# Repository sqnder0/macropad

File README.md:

# Soundpad

A 6-key media soundpad with a rotary encoder and a 0.91" OLED, built around a Seeed XIAO RP2040.

## Features
- 6 MX keys: volume up, mute, volume down, previous, play/pause, next
- Rotary encoder for volume, push to mute
- 128x32 OLED
- KMK firmware

## Schematic

## PCB

## Case
Two printed parts (case and plate), held together by four M3 screws.

## BOM

| Qty | Part | Notes |
| --- | --- | --- |
| 1 | Seeed XIAO RP2040 | Unsoldered, from the kit. Soldered flat to the back of the PCB |
| 6 | MX-style switch | From the kit |
| 6 | White blank DSA keycap | From the kit |
| 1 | EC11E rotary encoder with switch | From the kit, 20 mm D-shaft |
| 1 | Knob cap for the encoder | Not in the kit |
| 1 | 0.91" 128x32 OLED (SSD1306) | From the kit, pin order GND, VCC, SCL, SDA |
| 1 | 1x4 pin header (2.54 mm) | For the OLED |
| 4 | M3x16 mm screw | From the kit |
| 1 | 3D-printed case | Printed |
| 1 | 3D-printed plate | Printed |
| 1 | Custom PCB | Gerbers in `production/gerbers.zip` |

## Firmware
KMK, in `Firmware/main.py`.

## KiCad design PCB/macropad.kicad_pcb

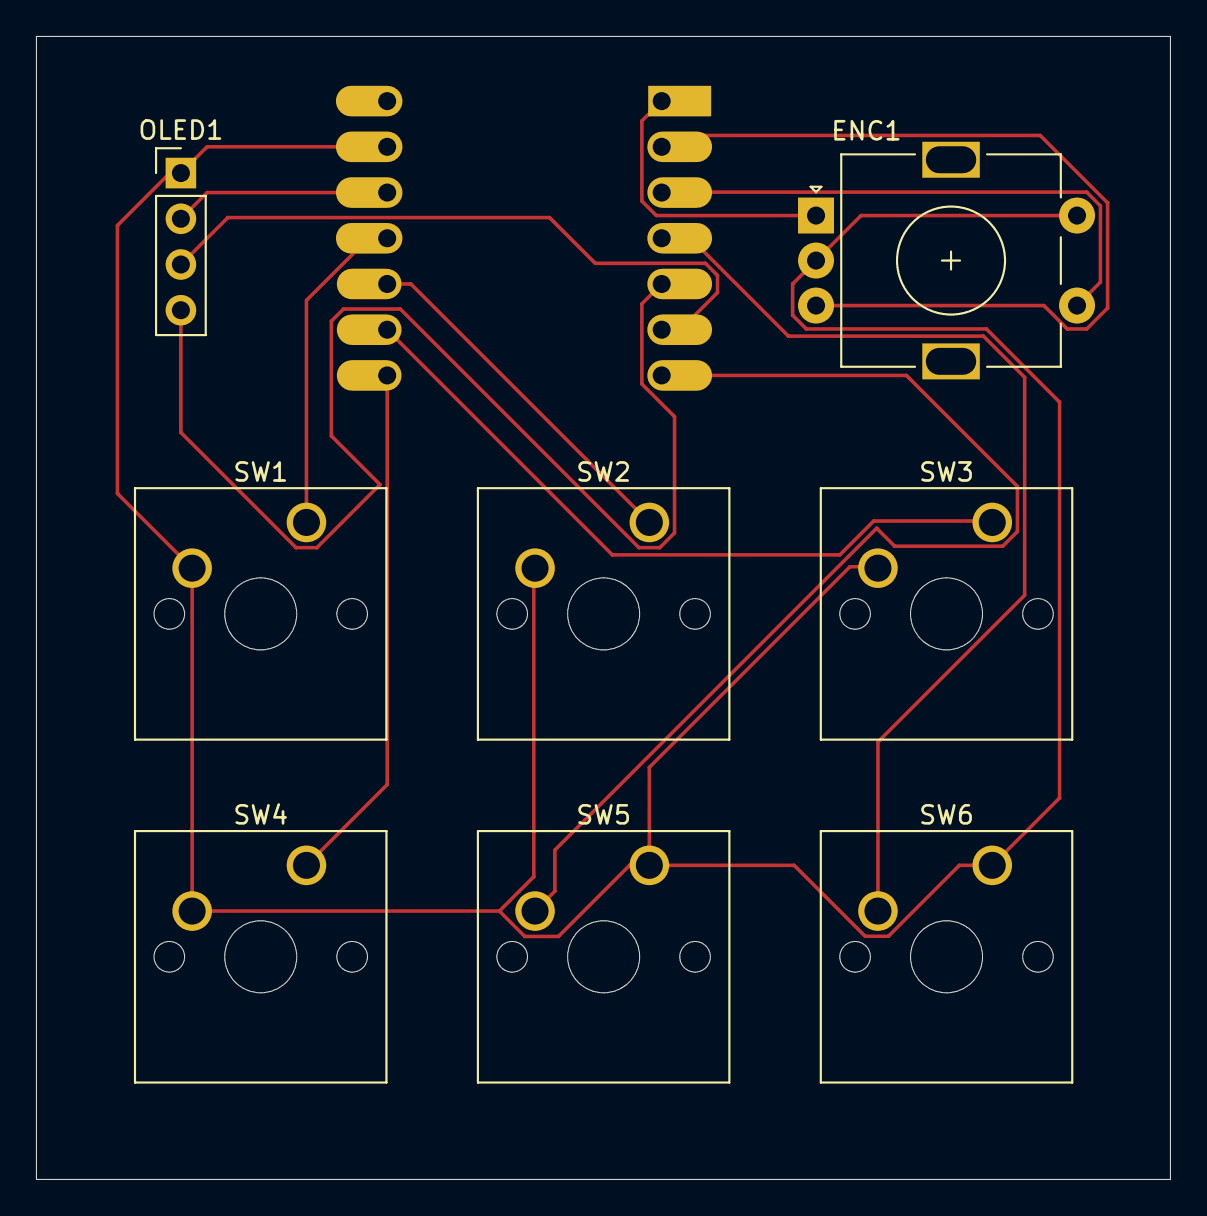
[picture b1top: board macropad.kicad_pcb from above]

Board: 2 copper layers, 63.0 x 63.5 mm, 9 parts (1 on the bottom side), 13 nets.

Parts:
ENC1: RotaryEncoder_Switch; RotaryEncoder_Alps_EC11E-Switch_Vertical_H20mm
OLED1: Conn_01x04_Pin; PinHeader_1x04_P2.54mm_Vertical
SW1, SW2, SW3, SW4, SW5, SW6: SW_Push; SW_Cherry_MX_1.00u_PCB
U1: MOUDLE-SEEEDUINO-XIAO; XIAO-Generic-Hybrid-14P-2.54-21X17.8MM

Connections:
/3V3: OLED1.2, U1.12 (3V3)
/Rot_A: ENC1.A, U1.1 (PA02_A0_D0)
/Rot_B: ENC1.B, U1.2 (PA4_A1_D1)
/Rot_S1: ENC1.S1, U1.3 (PA10_A2_D2)
/SCL: OLED1.3, U1.6 (PA9_A5_D5_SCL)
/SDA: OLED1.4, U1.5 (PA8_A4_D4_SDA)
GND: ENC1.C, ENC1.S2, OLED1.1, SW1.2, SW2.2, SW3.2, SW4.2, SW5.1, SW6.1, U1.13 (GND)
unnamed: SW2.1, U1.10 (PA5_A9_D9_MISO)
unnamed: SW1.1, U1.11 (PA6_A10_D10_MOSI)
unnamed: SW3.1, U1.9 (PA7_A8_D8_SCK)
unnamed: SW6.2, U1.4 (PA11_A3_D3)
unnamed: SW5.2, U1.7 (PB08_A6_D6_TX)
unnamed: SW4.1, U1.8 (PB09_A7_D7_RX)
